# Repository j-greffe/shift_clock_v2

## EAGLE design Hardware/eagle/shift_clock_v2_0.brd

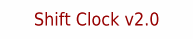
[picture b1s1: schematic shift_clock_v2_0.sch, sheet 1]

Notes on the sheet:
Shift Clock v2.0

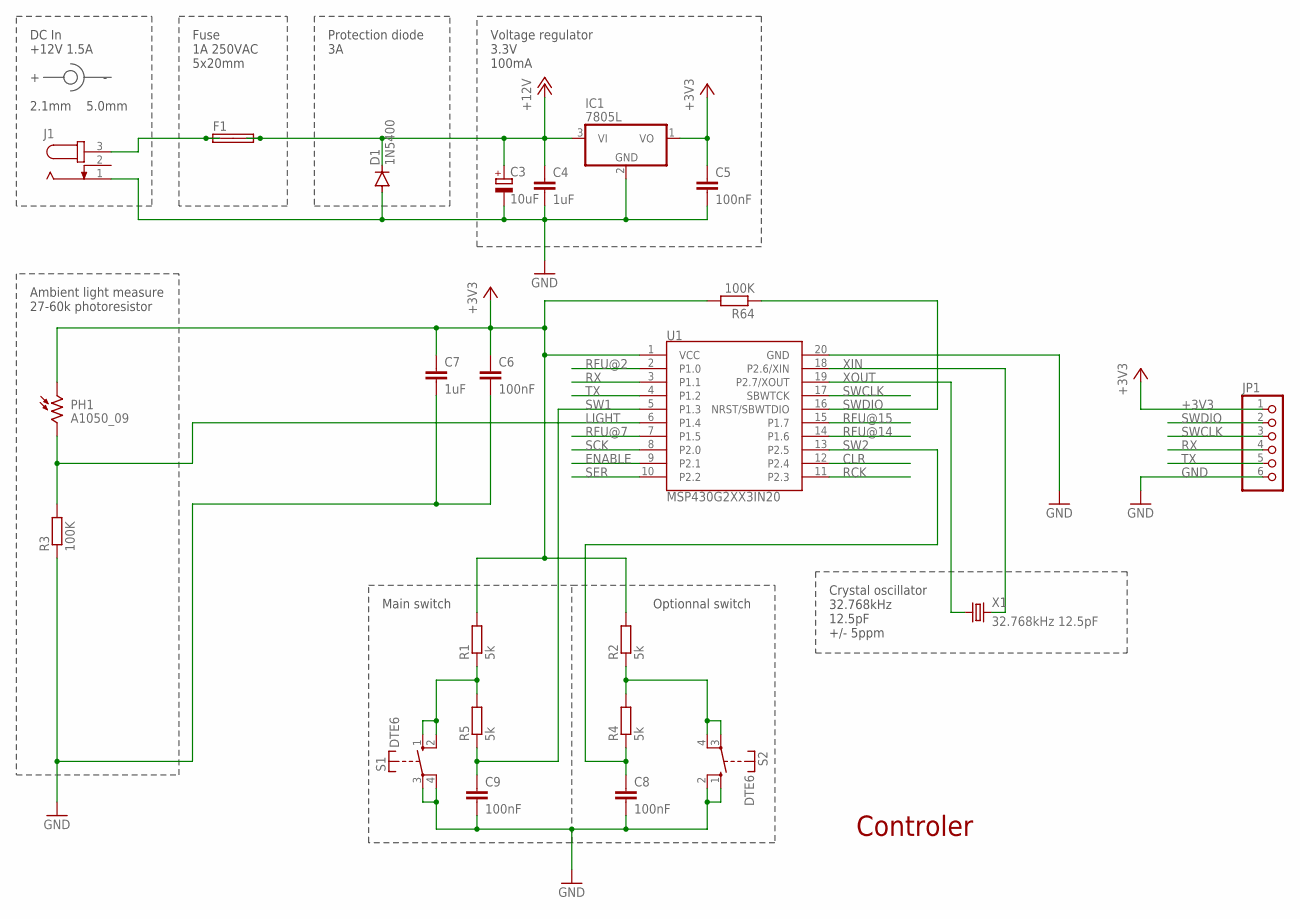
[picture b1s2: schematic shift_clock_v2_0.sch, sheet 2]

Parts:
C3: 10uF; E2,5-6
C4, C7: 1uF; C050-024X044
C5, C6, C8, C9: 100nF; C050-024X044
D1: 1N5400; DO201-15
F1: SHK20L
IC1: 7805L; TO92
J1: JACK-PLUG0; SPC4077
JP1: PINHD-1X6; 1X06
PH1: A1050_09; T0-46-A10XX
R1, R2, R4, R5: 5k; 0204/7
R3, R64: 100K; 0204/7
S1, S2: DTE6
U1: MSP430G2XX3IN20; DIL20
X1: 32.768kHz 12.5pF; TC26H

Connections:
+3V3: C5.1, C6.1, C7.1, IC1.1 (VO), JP1.1, PH1.1, R1.2, R2.2, R64.2, U1.1 (VCC); also elsewhere on the board
+12V: C3.+, C4.1, D1.C, F1.2A, F1.2B, IC1.3 (VI); also elsewhere on the board
CLR: U1.12 (P2.4); also elsewhere on the board
ENABLE: U1.9 (P2.1); also elsewhere on the board
GND: C3.-, C4.2, C5.2, C6.2, C7.2, C8.2, C9.2, D1.A, IC1.2 (GND), J1.1, JP1.6, R3.1, S1.3, S1.4, S2.1 (S), S2.2 (S), U1.20 (GND); also elsewhere on the board
LIGHT: PH1.2, R3.2, U1.6 (P1.4)
unnamed: F1.1A, F1.1B, J1.3
unnamed: R2.1, R4.2, S2.3, S2.4
unnamed: R1.1, R5.2, S1.1 (S), S1.2 (S)
RCK: U1.11 (P2.3); also elsewhere on the board
RFU@2: U1.2 (P1.0)
RFU@7: U1.7 (P1.5)
RFU@14: U1.14 (P1.6)
RFU@15: U1.15 (P1.7)
RX: JP1.4, U1.3 (P1.1)
SCK: U1.8 (P2.0); also elsewhere on the board
SER: U1.10 (P2.2); also elsewhere on the board
SW1: C9.1, R5.1, U1.5 (P1.3)
SW2: C8.1, R4.1, U1.13 (P2.5)
SWCLK: JP1.3, U1.17 (SBWTCK)
SWDIO: JP1.2, R64.1, U1.16 (NRST/SBWTDIO)
TX: JP1.5, U1.4 (P1.2)
XIN: U1.18 (P2.6/XIN), X1.2
XOUT: U1.19 (P2.7/XOUT), X1.1

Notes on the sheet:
Fuse 1A 250VAC 5x20mm
Controler
DC In +12V 1.5A + - 2.1mm 5.0mm
Protection diode 3A
Voltage regulator 3.3V 100mA
Ambient light measure 27-60k photoresistor
Main switch
Optionnal switch
Crystal oscillator 32.768kHz 12.5pF +/- 5ppm

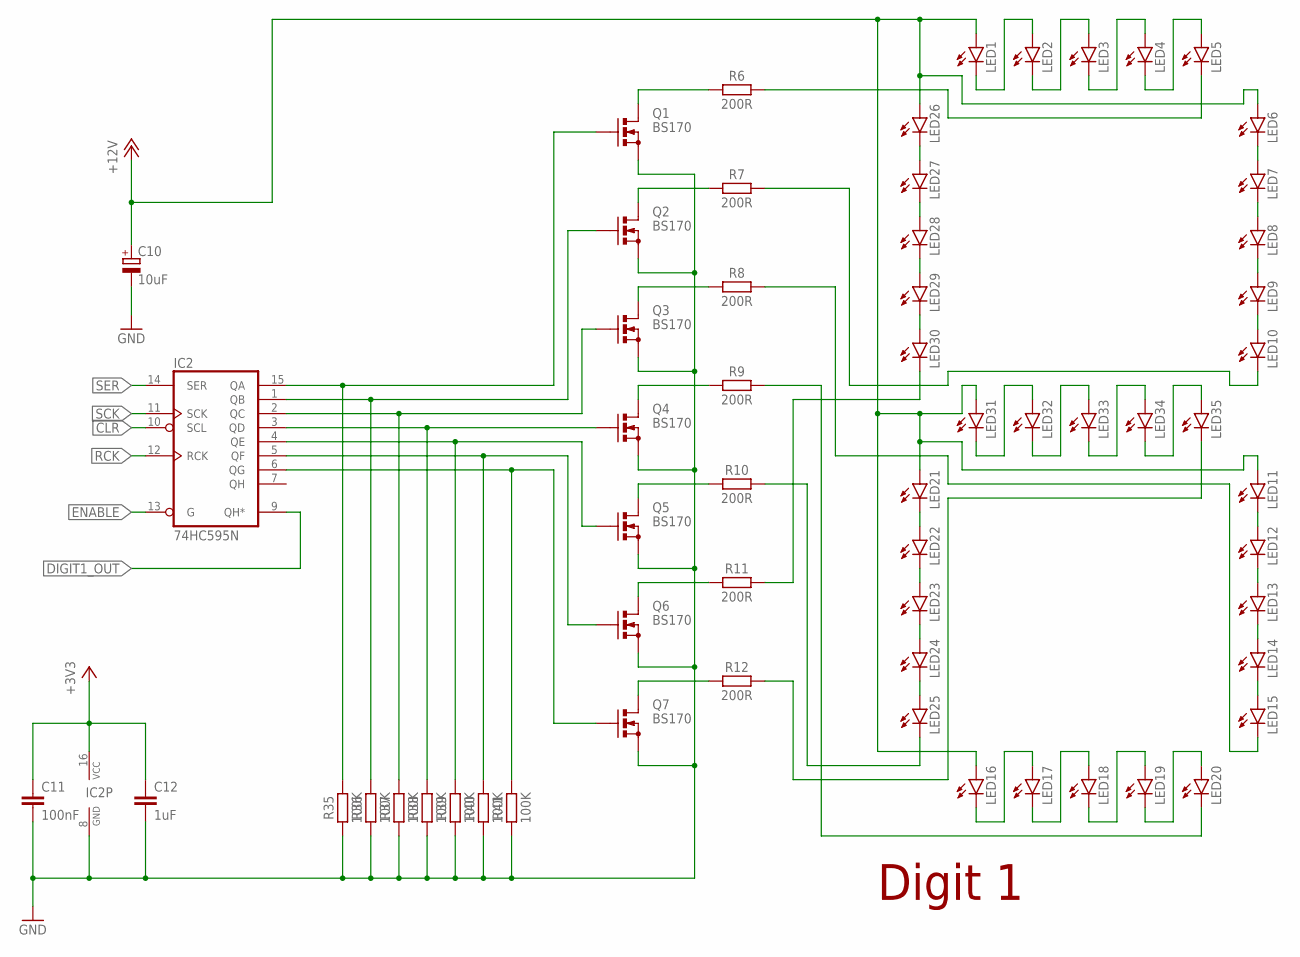
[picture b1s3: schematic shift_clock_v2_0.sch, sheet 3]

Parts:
C10: 10uF; E2,5-6
C11: 100nF; C050-024X044
C12: 1uF; C050-024X044
IC2: 74HC595N; DIL16
LED1, LED2, LED3, LED4, LED5, LED6, LED7, LED8, LED9, LED10, LED11, LED12, LED13, LED14, LED15, LED16, LED17, LED18, LED19, LED20, LED21, LED22, LED23, LED24, LED25, LED26, LED27, LED28, LED29, LED30, LED31, LED32, LED33, LED34, LED35: LED25X70
Q1, Q2, Q3, Q4, Q5, Q6, Q7: BS170; SOT54E
R6, R7, R8, R9, R10, R11, R12: 200R; 0204/7
R35, R36, R37, R38, R39, R40, R41: 100K; 0204/7

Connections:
+3V3: C11.1, C12.1, IC2.16 (VCC); also elsewhere on the board
+12V: C10.+, LED1.A, LED6.A, LED11.A, LED16.A, LED21.A, LED26.A, LED31.A; also elsewhere on the board
CLR: IC2.10 (SCL); also elsewhere on the board
DIGIT1_OUT: IC2.9 (QH*); also elsewhere on the board
ENABLE: IC2.13 (G); also elsewhere on the board
GND: C10.-, C11.2, C12.2, IC2.8 (GND), Q1.S, Q2.S, Q3.S, Q4.S, Q5.S, Q6.S, Q7.S, R35.1, R36.1, R37.1, R38.1, R39.1, R40.1, R41.1; also elsewhere on the board
unnamed: LED1.K (C), LED2.A
unnamed: LED2.K (C), LED3.A
unnamed: LED3.K (C), LED4.A
unnamed: LED4.K (C), LED5.A
unnamed: LED6.K (C), LED7.A
unnamed: LED7.K (C), LED8.A
unnamed: LED8.K (C), LED9.A
unnamed: LED9.K (C), LED10.A
unnamed: LED26.K (C), LED27.A
unnamed: LED27.K (C), LED28.A
unnamed: LED28.K (C), LED29.A
unnamed: LED29.K (C), LED30.A
unnamed: LED31.K (C), LED32.A
unnamed: LED32.K (C), LED33.A
unnamed: LED33.K (C), LED34.A
unnamed: LED34.K (C), LED35.A
unnamed: LED21.K (C), LED22.A
unnamed: LED22.K (C), LED23.A
unnamed: LED23.K (C), LED24.A
unnamed: LED24.K (C), LED25.A
unnamed: LED11.K (C), LED12.A
unnamed: LED12.K (C), LED13.A
unnamed: LED13.K (C), LED14.A
unnamed: LED14.K (C), LED15.A
unnamed: LED16.K (C), LED17.A
unnamed: LED17.K (C), LED18.A
unnamed: LED18.K (C), LED19.A
unnamed: LED19.K (C), LED20.A
unnamed: IC2.15 (QA), Q1.G, R35.2
unnamed: IC2.1 (QB), Q2.G, R36.2
unnamed: IC2.2 (QC), Q3.G, R37.2
unnamed: IC2.3 (QD), Q4.G, R38.2
unnamed: IC2.4 (QE), Q5.G, R39.2
unnamed: IC2.5 (QF), Q6.G, R40.2
unnamed: IC2.6 (QG), Q7.G, R41.2
unnamed: Q1.D, R6.1
unnamed: Q2.D, R7.1
unnamed: Q3.D, R8.1
unnamed: Q4.D, R9.1
unnamed: Q5.D, R10.1
unnamed: Q6.D, R11.1
unnamed: Q7.D, R12.1
unnamed: LED5.K (C), R6.2
unnamed: LED10.K (C), R7.2
unnamed: LED15.K (C), R8.2
unnamed: LED20.K (C), R9.2
unnamed: LED25.K (C), R10.2
unnamed: LED30.K (C), R11.2
unnamed: LED35.K (C), R12.2
RCK: IC2.12 (RCK); also elsewhere on the board
SCK: IC2.11 (SCK); also elsewhere on the board
SER: IC2.14 (SER); also elsewhere on the board

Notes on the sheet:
Digit 1

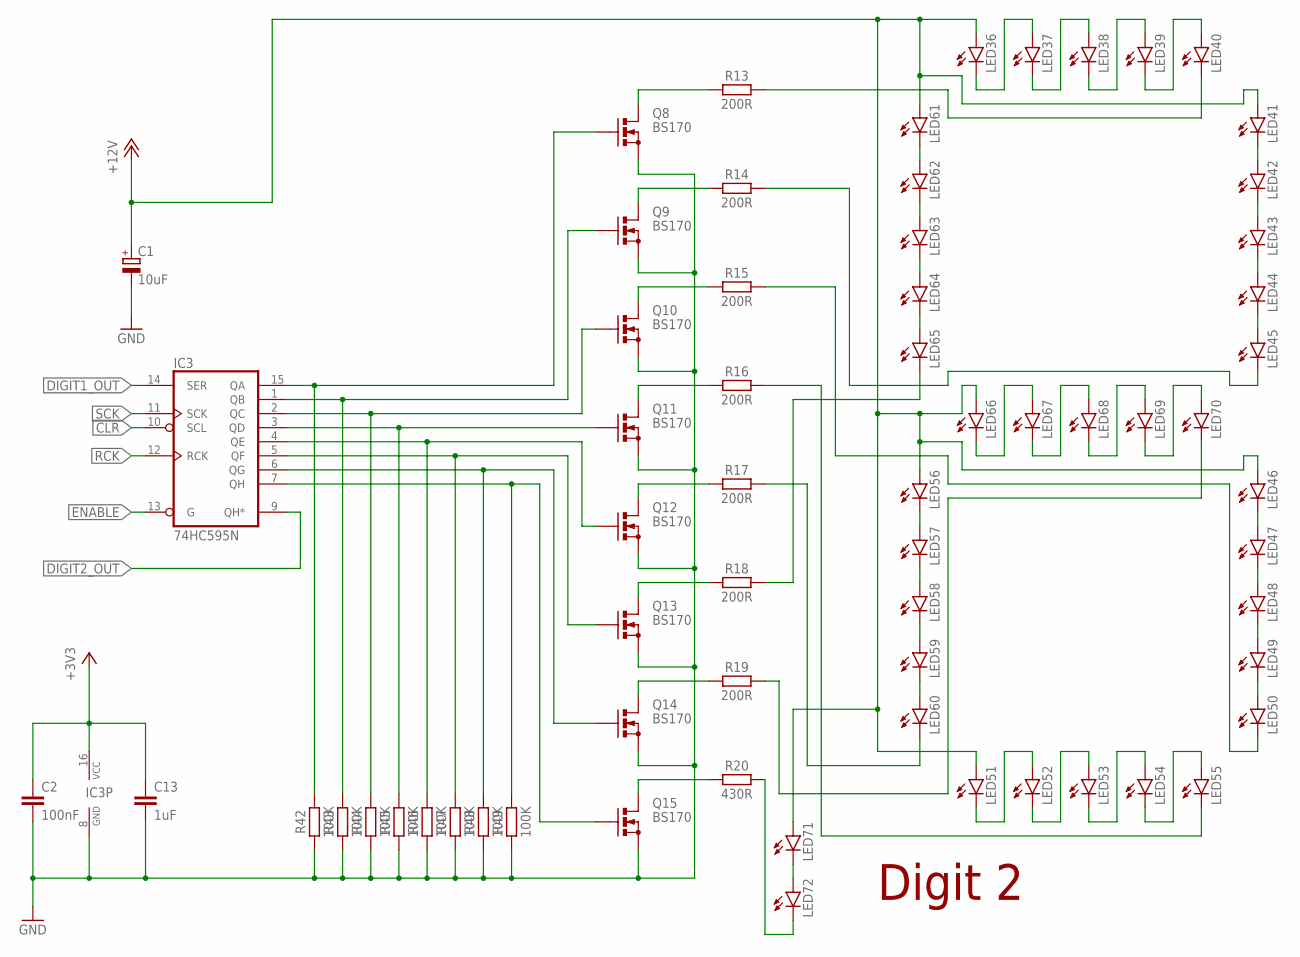
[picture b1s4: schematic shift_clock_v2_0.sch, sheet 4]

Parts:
C1: 10uF; E2,5-6
C2: 100nF; C050-024X044
C13: 1uF; C050-024X044
IC3: 74HC595N; DIL16
LED36, LED37, LED38, LED39, LED40, LED41, LED42, LED43, LED44, LED45, LED46, LED47, LED48, LED49, LED50, LED51, LED52, LED53, LED54, LED55, LED56, LED57, LED58, LED59, LED60, LED61, LED62, LED63, LED64, LED65, LED66, LED67, LED68, LED69, LED70, LED71, LED72: LED25X70
Q8, Q9, Q10, Q11, Q12, Q13, Q14, Q15: BS170; SOT54E
R13, R14, R15, R16, R17, R18, R19: 200R; 0204/7
R20: 430R; 0204/7
R42, R43, R44, R45, R46, R47, R48, R49: 100K; 0204/7

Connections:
+3V3: C2.1, C13.1, IC3.16 (VCC); also elsewhere on the board
+12V: C1.+, LED36.A, LED41.A, LED46.A, LED51.A, LED56.A, LED61.A, LED66.A, LED71.A; also elsewhere on the board
CLR: IC3.10 (SCL); also elsewhere on the board
DIGIT1_OUT: IC3.14 (SER); also elsewhere on the board
DIGIT2_OUT: IC3.9 (QH*); also elsewhere on the board
ENABLE: IC3.13 (G); also elsewhere on the board
GND: C1.-, C2.2, C13.2, IC3.8 (GND), Q8.S, Q9.S, Q10.S, Q11.S, Q12.S, Q13.S, Q14.S, Q15.S, R42.1, R43.1, R44.1, R45.1, R46.1, R47.1, R48.1, R49.1; also elsewhere on the board
unnamed: LED36.K (C), LED37.A
unnamed: LED37.K (C), LED38.A
unnamed: LED38.K (C), LED39.A
unnamed: LED39.K (C), LED40.A
unnamed: LED41.K (C), LED42.A
unnamed: LED42.K (C), LED43.A
unnamed: LED43.K (C), LED44.A
unnamed: LED44.K (C), LED45.A
unnamed: LED61.K (C), LED62.A
unnamed: LED62.K (C), LED63.A
unnamed: LED63.K (C), LED64.A
unnamed: LED64.K (C), LED65.A
unnamed: LED66.K (C), LED67.A
unnamed: LED67.K (C), LED68.A
unnamed: LED68.K (C), LED69.A
unnamed: LED69.K (C), LED70.A
unnamed: LED56.K (C), LED57.A
unnamed: LED57.K (C), LED58.A
unnamed: LED58.K (C), LED59.A
unnamed: LED59.K (C), LED60.A
unnamed: LED46.K (C), LED47.A
unnamed: LED47.K (C), LED48.A
unnamed: LED48.K (C), LED49.A
unnamed: LED49.K (C), LED50.A
unnamed: LED51.K (C), LED52.A
unnamed: LED52.K (C), LED53.A
unnamed: LED53.K (C), LED54.A
unnamed: LED54.K (C), LED55.A
unnamed: IC3.15 (QA), Q8.G, R42.2
unnamed: IC3.1 (QB), Q9.G, R43.2
unnamed: IC3.2 (QC), Q10.G, R44.2
unnamed: IC3.3 (QD), Q11.G, R45.2
unnamed: IC3.4 (QE), Q12.G, R46.2
unnamed: IC3.5 (QF), Q13.G, R47.2
unnamed: IC3.6 (QG), Q14.G, R48.2
unnamed: Q8.D, R13.1
unnamed: Q9.D, R14.1
unnamed: Q10.D, R15.1
unnamed: Q11.D, R16.1
unnamed: Q12.D, R17.1
unnamed: Q13.D, R18.1
unnamed: Q14.D, R19.1
unnamed: LED40.K (C), R13.2
unnamed: LED45.K (C), R14.2
unnamed: LED50.K (C), R15.2
unnamed: LED55.K (C), R16.2
unnamed: LED60.K (C), R17.2
unnamed: LED65.K (C), R18.2
unnamed: LED70.K (C), R19.2
unnamed: LED71.K (C), LED72.A
unnamed: LED72.K (C), R20.2
unnamed: Q15.D, R20.1
unnamed: IC3.7 (QH), Q15.G, R49.2
RCK: IC3.12 (RCK); also elsewhere on the board
SCK: IC3.11 (SCK); also elsewhere on the board

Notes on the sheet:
Digit 2

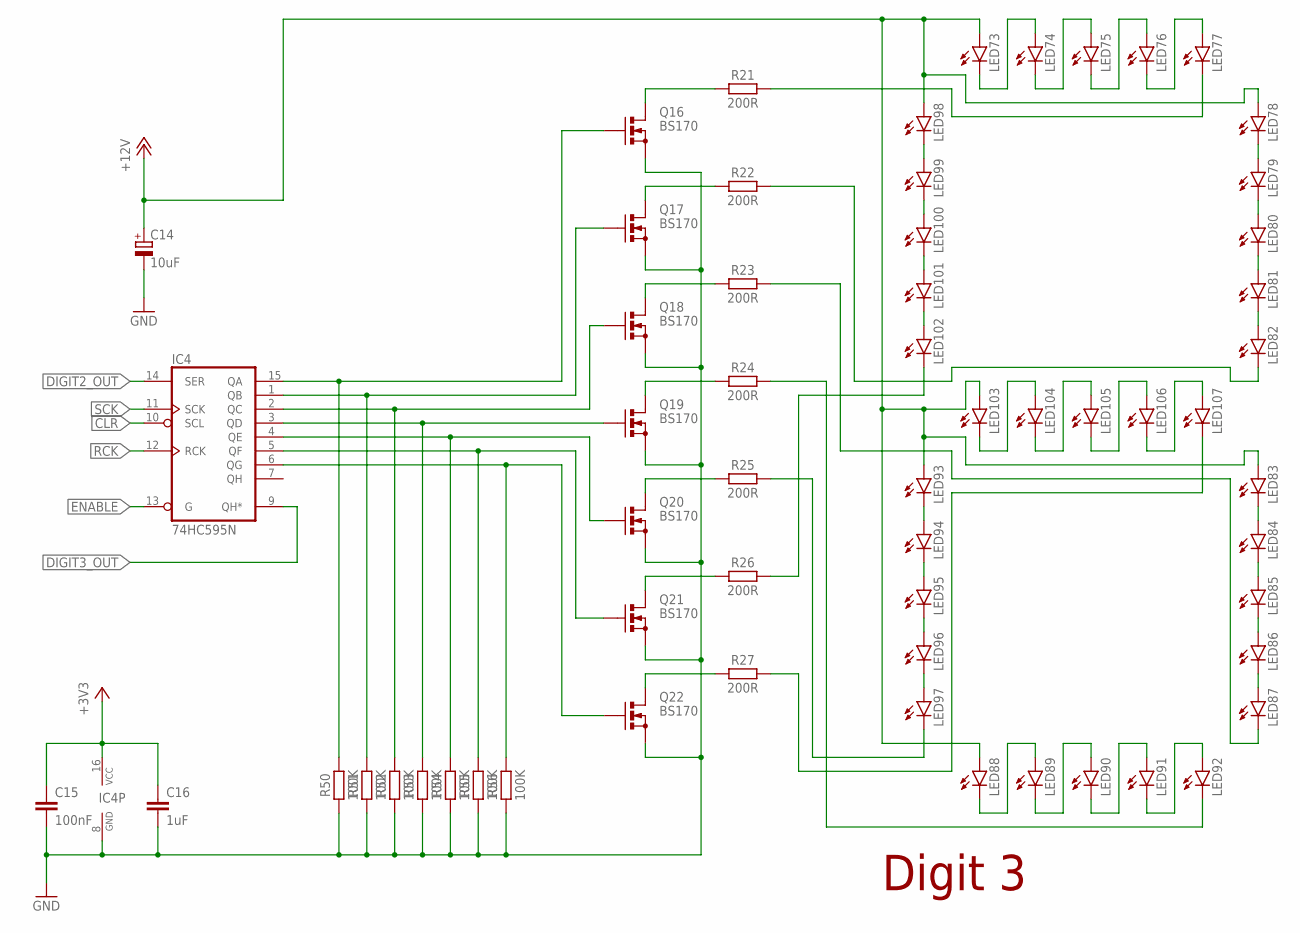
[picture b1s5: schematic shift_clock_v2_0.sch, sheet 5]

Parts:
C14: 10uF; E2,5-6
C15: 100nF; C050-024X044
C16: 1uF; C050-024X044
IC4: 74HC595N; DIL16
LED73, LED74, LED75, LED76, LED77, LED78, LED79, LED80, LED81, LED82, LED83, LED84, LED85, LED86, LED87, LED88, LED89, LED90, LED91, LED92, LED93, LED94, LED95, LED96, LED97, LED98, LED99, LED100, LED101, LED102, LED103, LED104, LED105, LED106, LED107: LED25X70
Q16, Q17, Q18, Q19, Q20, Q21, Q22: BS170; SOT54E
R21, R22, R23, R24, R25, R26, R27: 200R; 0204/7
R50, R51, R52, R53, R54, R55, R56: 100K; 0204/7

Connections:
+3V3: C15.1, C16.1, IC4.16 (VCC); also elsewhere on the board
+12V: C14.+, LED73.A, LED78.A, LED83.A, LED88.A, LED93.A, LED98.A, LED103.A; also elsewhere on the board
CLR: IC4.10 (SCL); also elsewhere on the board
DIGIT2_OUT: IC4.14 (SER); also elsewhere on the board
DIGIT3_OUT: IC4.9 (QH*); also elsewhere on the board
ENABLE: IC4.13 (G); also elsewhere on the board
GND: C14.-, C15.2, C16.2, IC4.8 (GND), Q16.S, Q17.S, Q18.S, Q19.S, Q20.S, Q21.S, Q22.S, R50.1, R51.1, R52.1, R53.1, R54.1, R55.1, R56.1; also elsewhere on the board
unnamed: LED73.K (C), LED74.A
unnamed: LED74.K (C), LED75.A
unnamed: LED75.K (C), LED76.A
unnamed: LED76.K (C), LED77.A
unnamed: LED78.K (C), LED79.A
unnamed: LED79.K (C), LED80.A
unnamed: LED80.K (C), LED81.A
unnamed: LED81.K (C), LED82.A
unnamed: LED98.K (C), LED99.A
unnamed: LED99.K (C), LED100.A
unnamed: LED100.K (C), LED101.A
unnamed: LED101.K (C), LED102.A
unnamed: LED103.K (C), LED104.A
unnamed: LED104.K (C), LED105.A
unnamed: LED105.K (C), LED106.A
unnamed: LED106.K (C), LED107.A
unnamed: LED93.K (C), LED94.A
unnamed: LED94.K (C), LED95.A
unnamed: LED95.K (C), LED96.A
unnamed: LED96.K (C), LED97.A
unnamed: LED83.K (C), LED84.A
unnamed: LED84.K (C), LED85.A
unnamed: LED85.K (C), LED86.A
unnamed: LED86.K (C), LED87.A
unnamed: LED88.K (C), LED89.A
unnamed: LED89.K (C), LED90.A
unnamed: LED90.K (C), LED91.A
unnamed: LED91.K (C), LED92.A
unnamed: IC4.15 (QA), Q16.G, R50.2
unnamed: IC4.1 (QB), Q17.G, R51.2
unnamed: IC4.2 (QC), Q18.G, R52.2
unnamed: IC4.3 (QD), Q19.G, R53.2
unnamed: IC4.4 (QE), Q20.G, R54.2
unnamed: IC4.6 (QG), Q22.G, R56.2
unnamed: Q16.D, R21.1
unnamed: Q17.D, R22.1
unnamed: Q18.D, R23.1
unnamed: Q19.D, R24.1
unnamed: Q20.D, R25.1
unnamed: Q21.D, R26.1
unnamed: Q22.D, R27.1
unnamed: LED77.K (C), R21.2
unnamed: LED82.K (C), R22.2
unnamed: LED87.K (C), R23.2
unnamed: LED92.K (C), R24.2
unnamed: LED97.K (C), R25.2
unnamed: LED102.K (C), R26.2
unnamed: LED107.K (C), R27.2
unnamed: IC4.5 (QF), Q21.G, R55.2
RCK: IC4.12 (RCK); also elsewhere on the board
SCK: IC4.11 (SCK); also elsewhere on the board

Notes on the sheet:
Digit 3

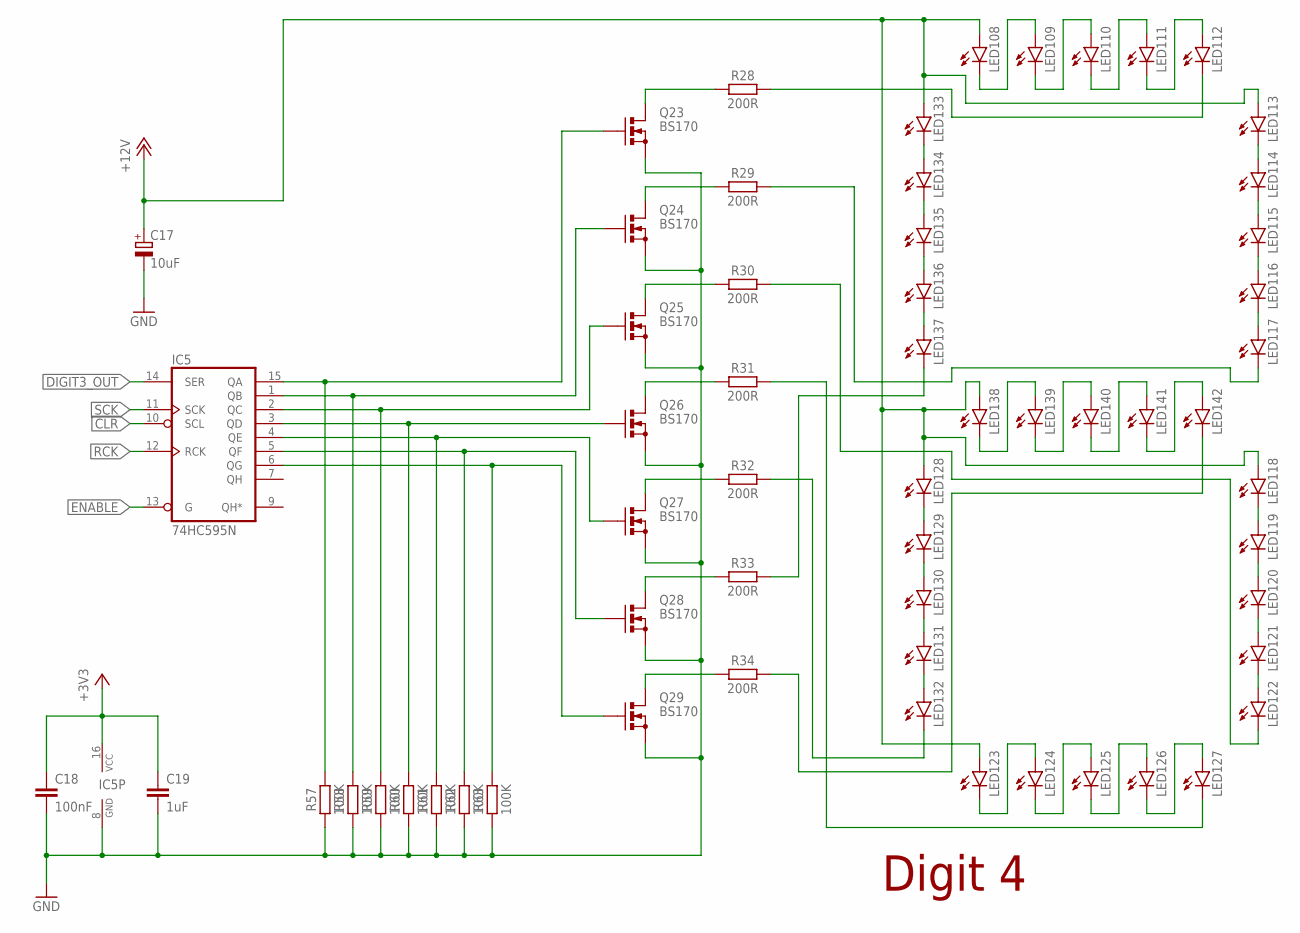
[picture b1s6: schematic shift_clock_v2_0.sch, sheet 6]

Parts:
C17: 10uF; E2,5-6
C18: 100nF; C050-024X044
C19: 1uF; C050-024X044
IC5: 74HC595N; DIL16
LED108, LED109, LED110, LED111, LED112, LED113, LED114, LED115, LED116, LED117, LED118, LED119, LED120, LED121, LED122, LED123, LED124, LED125, LED126, LED127, LED128, LED129, LED130, LED131, LED132, LED133, LED134, LED135, LED136, LED137, LED138, LED139, LED140, LED141, LED142: LED25X70
Q23, Q24, Q25, Q26, Q27, Q28, Q29: BS170; SOT54E
R28, R29, R30, R31, R32, R33, R34: 200R; 0204/7
R57, R58, R59, R60, R61, R62, R63: 100K; 0204/7

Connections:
+3V3: C18.1, C19.1, IC5.16 (VCC); also elsewhere on the board
+12V: C17.+, LED108.A, LED113.A, LED118.A, LED123.A, LED128.A, LED133.A, LED138.A; also elsewhere on the board
CLR: IC5.10 (SCL); also elsewhere on the board
DIGIT3_OUT: IC5.14 (SER); also elsewhere on the board
ENABLE: IC5.13 (G); also elsewhere on the board
GND: C17.-, C18.2, C19.2, IC5.8 (GND), Q23.S, Q24.S, Q25.S, Q26.S, Q27.S, Q28.S, Q29.S, R57.1, R58.1, R59.1, R60.1, R61.1, R62.1, R63.1; also elsewhere on the board
unnamed: LED108.K (C), LED109.A
unnamed: LED109.K (C), LED110.A
unnamed: LED110.K (C), LED111.A
unnamed: LED111.K (C), LED112.A
unnamed: LED113.K (C), LED114.A
unnamed: LED114.K (C), LED115.A
unnamed: LED115.K (C), LED116.A
unnamed: LED116.K (C), LED117.A
unnamed: LED133.K (C), LED134.A
unnamed: LED134.K (C), LED135.A
unnamed: LED135.K (C), LED136.A
unnamed: LED136.K (C), LED137.A
unnamed: LED138.K (C), LED139.A
unnamed: LED139.K (C), LED140.A
unnamed: LED140.K (C), LED141.A
unnamed: LED141.K (C), LED142.A
unnamed: LED128.K (C), LED129.A
unnamed: LED129.K (C), LED130.A
unnamed: LED130.K (C), LED131.A
unnamed: LED131.K (C), LED132.A
unnamed: LED118.K (C), LED119.A
unnamed: LED119.K (C), LED120.A
unnamed: LED120.K (C), LED121.A
unnamed: LED121.K (C), LED122.A
unnamed: LED123.K (C), LED124.A
unnamed: LED124.K (C), LED125.A
unnamed: LED125.K (C), LED126.A
unnamed: LED126.K (C), LED127.A
unnamed: IC5.15 (QA), Q23.G, R57.2
unnamed: IC5.1 (QB), Q24.G, R58.2
unnamed: IC5.2 (QC), Q25.G, R59.2
unnamed: IC5.3 (QD), Q26.G, R60.2
unnamed: IC5.4 (QE), Q27.G, R61.2
unnamed: IC5.5 (QF), Q28.G, R62.2
unnamed: IC5.6 (QG), Q29.G, R63.2
unnamed: Q23.D, R28.1
unnamed: Q24.D, R29.1
unnamed: Q25.D, R30.1
unnamed: Q26.D, R31.1
unnamed: Q27.D, R32.1
unnamed: Q28.D, R33.1
unnamed: Q29.D, R34.1
unnamed: LED112.K (C), R28.2
unnamed: LED117.K (C), R29.2
unnamed: LED122.K (C), R30.2
unnamed: LED127.K (C), R31.2
unnamed: LED132.K (C), R32.2
unnamed: LED137.K (C), R33.2
unnamed: LED142.K (C), R34.2
RCK: IC5.12 (RCK); also elsewhere on the board
SCK: IC5.11 (SCK); also elsewhere on the board

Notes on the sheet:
Digit 4

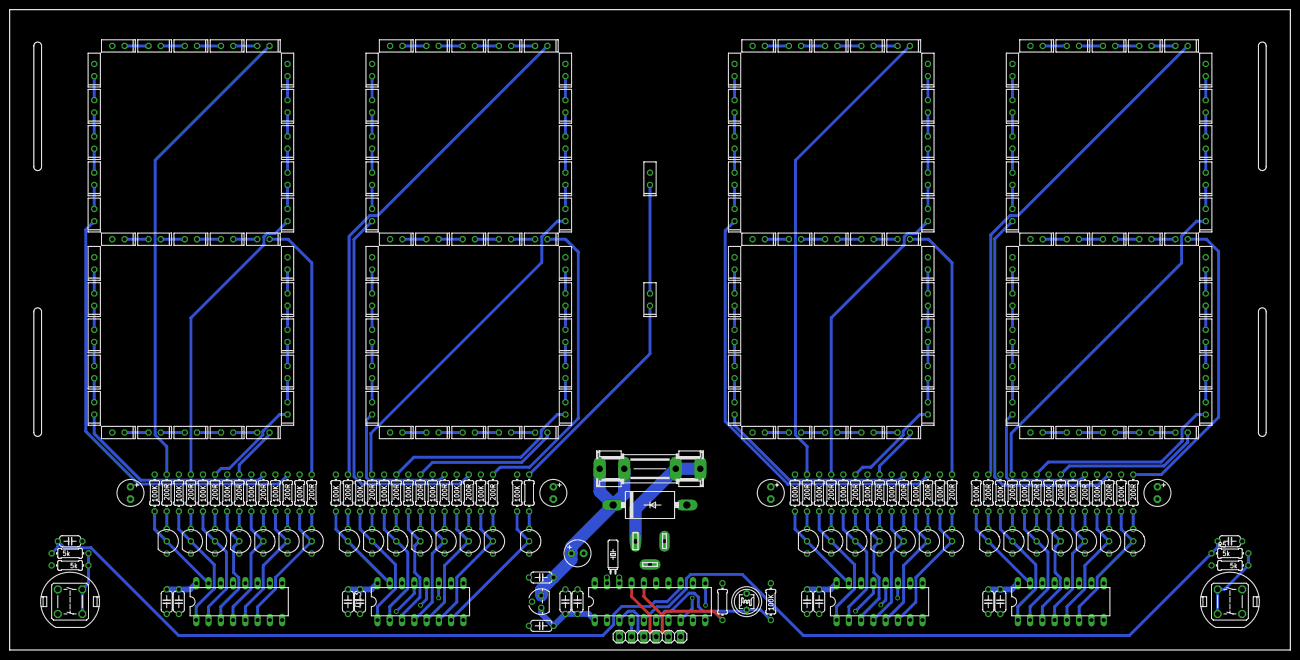
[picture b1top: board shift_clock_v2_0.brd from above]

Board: 4 copper layers, 265.0 x 132.5 mm, 268 parts (1 on the bottom side), 223 nets.

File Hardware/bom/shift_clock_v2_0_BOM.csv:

"Qty";"Value";"Device";"Package";"Parts";"Description";"MF";"MPN";"OC_FARNELL";"OC_NEWARK";"POPULARITY";"SPICEPREFIX";
"1";"";"JACK-PLUG0";"SPC4077";"J1";"DC POWER JACK";"";"";"unknown";"unknown";"0";"";
"142";"";"LED25X70";"LED25X70";"LED1, LED2, LED3, LED4, LED5, LED6, LED7, LED8, LED9, LED10, LED11, LED12, LED13, LED14, LED15, LED16, LED17, LED18, LED19, LED20, LED21, LED22, LED23, LED24, LED25, LED26, LED27, LED28, LED29, LED30, LED31, LED32, LED33, LED34, LED35, LED36, LED37, LED38, LED39, LED40, LED41, LED42, LED43, LED44, LED45, LED46, LED47, LED48, LED49, LED50, LED51, LED52, LED53, LED54, LED55, LED56, LED57, LED58, LED59, LED60, LED61, LED62, LED63, LED64, LED65, LED66, LED67, LED68, LED69, LED70, LED71, LED72, LED73, LED74, LED75, LED76, LED77, LED78, LED79, LED80, LED81, LED82, LED83, LED84, LED85, LED86, LED87, LED88, LED89, LED90, LED91, LED92, LED93, LED94, LED95, LED96, LED97, LED98, LED99, LED100, LED101, LED102, LED103, LED104, LED105, LED106, LED107, LED108, LED109, LED110, LED111, LED112, LED113, LED114, LED115, LED116, LED117, LED118, LED119, LED120, LED121, LED122, LED123, LED124, LED125, LED126, LED127, LED128, LED129, LED130, LED131, LED132, LED133, LED134, LED135, LED136, LED137, LED138, LED139, LED140, LED141, LED142";"LED";"";"";"";"";"";"";
"1";"";"PINHD-1X6";"1X06";"JP1";"PIN HEADER";"";"";"";"";"79";"";
"1";"";"SHK20L";"SHK20L";"F1";"FUSE HOLDER 5 x 20 mm, SH contact, SHH1 Schukat, E1073 Buerklin";"";"";"unknown";"unknown";"3";"";
"31";"100K";"R-EU_0204/7";"0204/7";"R3, R35, R36, R37, R38, R39, R40, R41, R42, R43, R44, R45, R46, R47, R48, R49, R50, R51, R52, R53, R54, R55, R56, R57, R58, R59, R60, R61, R62, R63, R64";"RESISTOR, European symbol";"";"";"";"";"0";"R";
"8";"100nF";"C-EU050-024X044";"C050-024X044";"C2, C5, C6, C8, C9, C11, C15, C18";"CAPACITOR, European symbol";"";"";"";"";"33";"C";
"5";"10uF";"CPOL-EUE2.5-6";"E2,5-6";"C1, C3, C10, C14, C17";"POLARIZED CAPACITOR, European symbol";"";"";"";"";"26";"C";
"1";"1N5400";"1N5400";"DO201-15";"D1";"DIODE";"";"";"";"";"2";"";
"6";"1uF";"C-EU050-024X044";"C050-024X044";"C4, C7, C12, C13, C16, C19";"CAPACITOR, European symbol";"";"";"";"";"33";"C";
"28";"200R";"R-EU_0204/7";"0204/7";"R6, R7, R8, R9, R10, R11, R12, R13, R14, R15, R16, R17, R18, R19, R21, R22, R23, R24, R25, R26, R27, R28, R29, R30, R31, R32, R33, R34";"RESISTOR, European symbol";"";"";"";"";"0";"R";
"1";"32.768kHz 12.5pF";"CRYSTALTC26H";"TC26H";"X1";"CRYSTAL";"";"";"unknown";"unknown";"6";"";
"1";"430R";"R-EU_0204/7";"0204/7";"R20";"RESISTOR, European symbol";"";"";"";"";"0";"R";
"4";"5k";"R-EU_0204/7";"0204/7";"R1, R2, R4, R5";"RESISTOR, European symbol";"";"";"";"";"0";"R";
"4";"74HC595N";"74HC595N";"DIL16";"IC2, IC3, IC4, IC5";"8-bit SHIFT REGISTER, output latch";"";"";"";"";"0";"";
"1";"7805L";"7805L";"TO92";"IC1";"Positive VOLTAGE REGULATOR";"";"";"";"";"0";"";
"1";"A1050_09";"A1050_09";"T0-46-A10XX";"PH1";"Sensor Robust Light Sensing Applications";"";"";"";"";"0";"";
"29";"BS170";"BS170";"SOT54E";"Q1, Q2, Q3, Q4, Q5, Q6, Q7, Q8, Q9, Q10, Q11, Q12, Q13, Q14, Q15, Q16, Q17, Q18, Q19, Q20, Q21, Q22, Q23, Q24, Q25, Q26, Q27, Q28, Q29";"N-CHANNEL MOS FET";"";"";"";"";"5";"";
"2";"DTE6";"DTE6";"DTE6";"S1, S2";"ITT SWITCH";"";"";"";"";"0";"";
"1";"MSP430G2XX3IN20";"MSP430G2XX3IN20";"DIL20";"U1";"";"";"";"";"";"";"";

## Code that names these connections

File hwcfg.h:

#include "hal_gpio.h"
#include "shift_register_74hc595x.h"
#include "shift_digit.h"

// Port 1
#define IO_RFU2         HAL_IO_PACK(1, 0)
#define IO_RX           HAL_IO_PACK(1, 1)
#define IO_TX           HAL_IO_PACK(1, 2)
#define IO_BUTTON1      HAL_IO_PACK(1, 3)
#define IO_LIGHT        HAL_IO_PACK(1, 4)
#define IO_RFU7         HAL_IO_PACK(1, 5)
#define IO_RFU15        HAL_IO_PACK(1, 6)
#define IO_RFU16        HAL_IO_PACK(1, 7)

// Port 2
#define IO_ENA          HAL_IO_PACK(2, 1)
#define IO_SCK          HAL_IO_PACK(2, 0)
#define IO_SER          HAL_IO_PACK(2, 2)
#define IO_RCK          HAL_IO_PACK(2, 3)
#define IO_CLR          HAL_IO_PACK(2, 4)
#define IO_BUTTON2      HAL_IO_PACK(2, 5)
#define IO_XIN          HAL_IO_PACK(2, 6) // XXX Do not modify
#define IO_XOUT         HAL_IO_PACK(2, 7) // XXX Do not modify

extern const shift_register_74hc595x_hwcfg_t    k_shift_register_hwcfg;
extern const shift_digit_hwcfg_t                k_shift_digit_hwcfg;

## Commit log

2020-11-24 Initial commit.
2020-11-24 Updated driver
2020-11-25 Moved app specific content from drivers to here.
2020-11-28 Updated from shift_clock_v1.
2022-04-19 Added Hardware.
2022-04-19 Fixed submodules
2022-05-27 Fixed submodules.
2022-05-27 Fixed for good. (I hope)
